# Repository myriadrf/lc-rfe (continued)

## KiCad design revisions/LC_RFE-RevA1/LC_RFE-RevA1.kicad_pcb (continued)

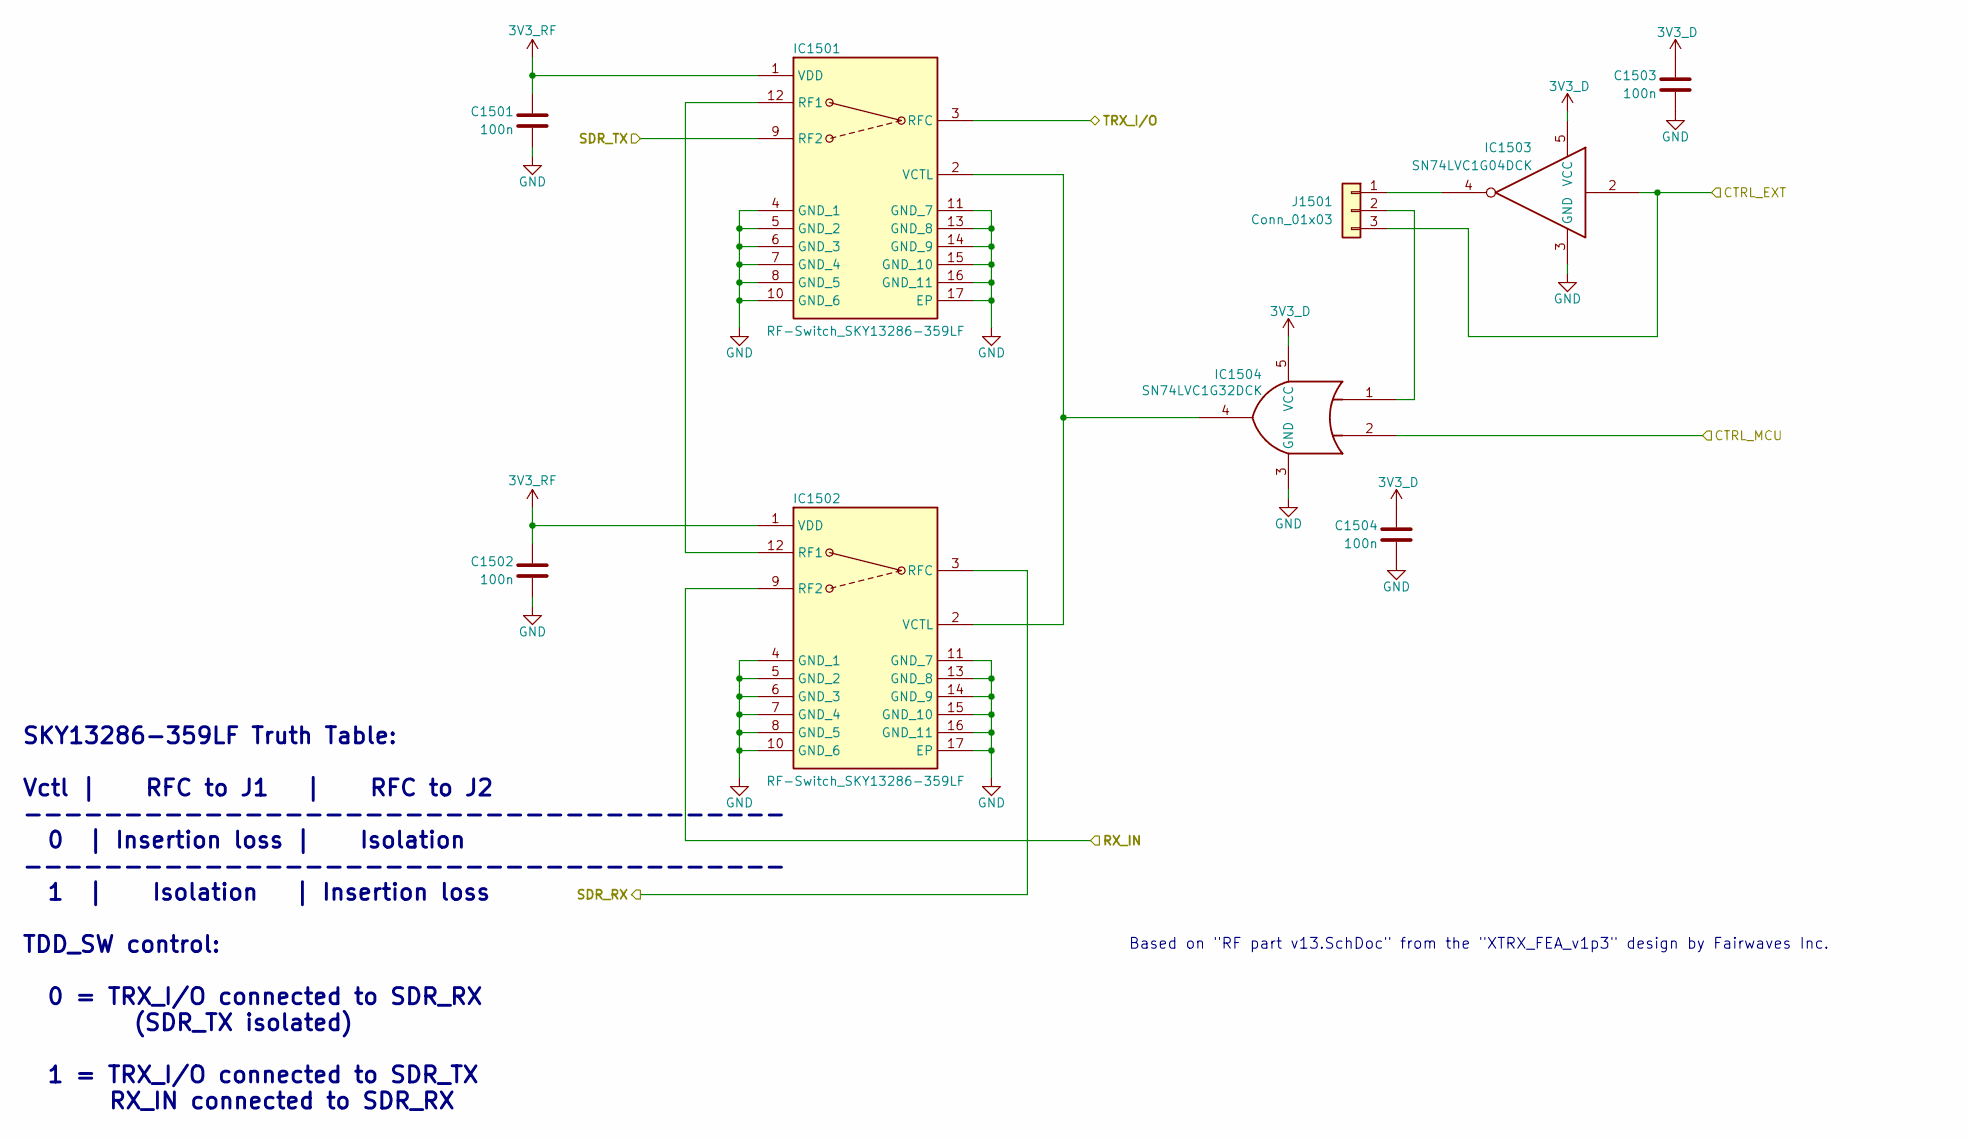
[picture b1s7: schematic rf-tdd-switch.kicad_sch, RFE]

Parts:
C1501, C1502, C1503, C1504: 100n; C_0402_1005Metric; JLCASSY C307331
IC1501, IC1502: RF-Switch_SKY13286-359LF; QFN65P400X400X100-17N-D; Manufacturer_Part_Number SKY13286-359LF; JLCASSY C3304168
IC1503: SN74LVC1G04DCK; SOT-353_SC-70-5; JLCASSY C8207
IC1504: SN74LVC1G32DCK; SOT-353_SC-70-5; JLCASSY C7840
J1501: Conn_01x03; PinHeader_1x03_P2.54mm_Vertical

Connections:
3V3_D: C1503.1, C1504.1, IC1503.5 (VCC), IC1504.5 (VCC); also elsewhere on the board
3V3_RF: C1501.1, C1502.1, IC1501.1 (VDD), IC1502.1 (VDD); also elsewhere on the board
/MCU/STM32_PB6: IC1504.2; also elsewhere on the board
/RF/CH_A_RX: IC1502.9 (RF2); also elsewhere on the board
/RF/CH_A_TRX: IC1501.3 (RFC); also elsewhere on the board
/RF/LNA A/RF_IN: IC1502.3 (RFC); also elsewhere on the board
/RF/PA A/RF_OUT: IC1501.9 (RF2); also elsewhere on the board
GND: C1501.2, C1502.2, C1503.2, C1504.2, IC1501.4 (GND_1), IC1501.5 (GND_2), IC1501.6 (GND_3), IC1501.7 (GND_4), IC1501.8 (GND_5), IC1501.10 (GND_6), IC1501.11 (GND_7), IC1501.13 (GND_8), IC1501.14 (GND_9), IC1501.15 (GND_10), IC1501.16 (GND_11), IC1501.17 (EP), IC1502.4 (GND_1), IC1502.5 (GND_2), IC1502.6 (GND_3), IC1502.7 (GND_4), IC1502.8 (GND_5), IC1502.10 (GND_6), IC1502.11 (GND_7), IC1502.13 (GND_8), IC1502.14 (GND_9), IC1502.15 (GND_10), IC1502.16 (GND_11), IC1502.17 (EP), IC1503.3 (GND), IC1504.3 (GND); also elsewhere on the board
unnamed: IC1501.12 (RF1), IC1502.12 (RF1)
unnamed: IC1501.2 (VCTL), IC1502.2 (VCTL), IC1504.4
unnamed: IC1503.4, J1501.1
unnamed: IC1504.1, J1501.2
TDD_A_CTRL_EXT: IC1503.2, J1501.3; also elsewhere on the board

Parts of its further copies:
C1601, C1602, C1603, C1604: 100n; C_0402_1005Metric; JLCASSY C307331
IC1601, IC1602: RF-Switch_SKY13286-359LF; QFN65P400X400X100-17N-D; Manufacturer_Part_Number SKY13286-359LF; JLCASSY C3304168
IC1603: SN74LVC1G04DCK; SOT-353_SC-70-5; JLCASSY C8207
IC1604: SN74LVC1G32DCK; SOT-353_SC-70-5; JLCASSY C7840
J1601: Conn_01x03; PinHeader_1x03_P2.54mm_Vertical

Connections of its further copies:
3V3_D: C1603.1, C1604.1, IC1603.5 (VCC), IC1604.5 (VCC); also elsewhere on the board
3V3_RF: C1601.1, C1602.1, IC1601.1 (VDD), IC1602.1 (VDD); also elsewhere on the board
/MCU/STM32_PB4: IC1604.2; also elsewhere on the board
/RF/CH_B_RX: IC1602.9 (RF2); also elsewhere on the board
/RF/CH_B_TRX: IC1601.3 (RFC); also elsewhere on the board
/RF/LNA B/RF_IN: IC1602.3 (RFC); also elsewhere on the board
/RF/PA B/RF_OUT: IC1601.9 (RF2); also elsewhere on the board
GND: C1601.2, C1602.2, C1603.2, C1604.2, IC1601.4 (GND_1), IC1601.5 (GND_2), IC1601.6 (GND_3), IC1601.7 (GND_4), IC1601.8 (GND_5), IC1601.10 (GND_6), IC1601.11 (GND_7), IC1601.13 (GND_8), IC1601.14 (GND_9), IC1601.15 (GND_10), IC1601.16 (GND_11), IC1601.17 (EP), IC1602.4 (GND_1), IC1602.5 (GND_2), IC1602.6 (GND_3), IC1602.7 (GND_4), IC1602.8 (GND_5), IC1602.10 (GND_6), IC1602.11 (GND_7), IC1602.13 (GND_8), IC1602.14 (GND_9), IC1602.15 (GND_10), IC1602.16 (GND_11), IC1602.17 (EP), IC1603.3 (GND), IC1604.3 (GND); also elsewhere on the board
unnamed: IC1601.12 (RF1), IC1602.12 (RF1)
unnamed: IC1601.2 (VCTL), IC1602.2 (VCTL), IC1604.4
unnamed: IC1603.4, J1601.1
unnamed: IC1604.1, J1601.2
TDD_B_CTRL_EXT: IC1603.2, J1601.3; also elsewhere on the board

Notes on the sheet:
Based on "RF part v13.SchDoc" from the "XTRX_FEA_v1p3" design by Fairwaves Inc.
SKY13286-359LF Truth Table: Vctl | RFC to J1 | RFC to J2 -------------------------------------- 0 | Insertion loss | Isolation -------------------------------------- 1 | Isolation | Insertion loss TDD_SW control: 0 = TRX_I/O connected to SDR_RX (SDR_TX isolated) 1 = TRX_I/O connected to SDR_TX RX_I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

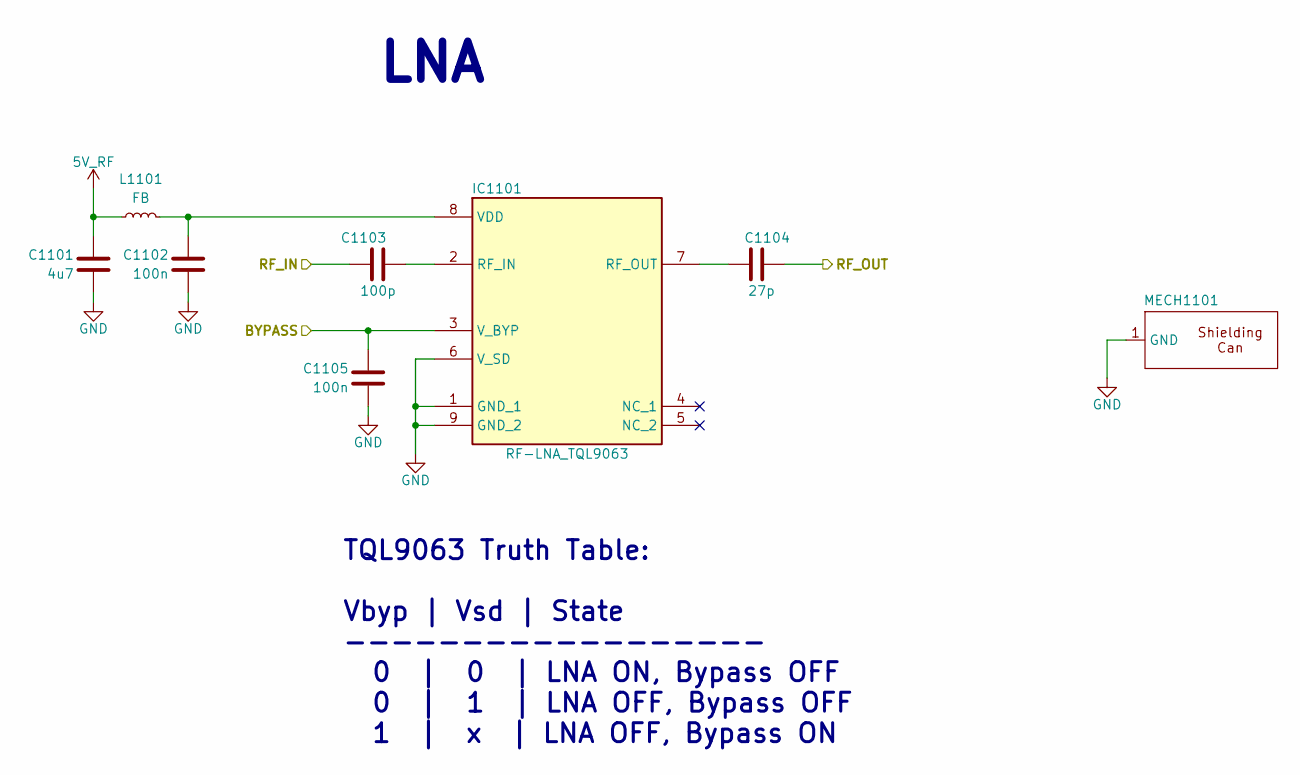
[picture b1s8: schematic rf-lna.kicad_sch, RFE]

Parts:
C1101: 4u7; C_0402_1005Metric; JLCASSY C23733
C1102, C1105: 100n; C_0402_1005Metric; JLCASSY C307331
C1103: 100p; C_0402_1005Metric; JLCASSY C77177
C1104: 27p; C_0402_1005Metric; JLCASSY C1557
IC1101: RF-LNA_TQL9063; SON50P200X200X90-9N; Manufacturer_Part_Number TQL9063; Mouser Part Number 772-TQL9063
L1101: FB; L_0402_1005Metric; JLCASSY C491491
MECH1101: Harwin_S03-15100300R+S0941-46R

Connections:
5V_RF: C1101.1, L1101.1; also elsewhere on the board
/MCU/STM32_PD1: C1105.1, IC1101.3 (V_BYP); also elsewhere on the board
/RF/LNA A/RF_IN: C1103.1; also elsewhere on the board
/RF/LNA A/RF_OUT: C1104.2; also elsewhere on the board
GND: C1101.2, C1102.2, C1105.2, IC1101.1 (GND_1), IC1101.6 (V_SD), IC1101.9 (GND_2), MECH1101.1 (GND); also elsewhere on the board
unnamed: C1103.2, IC1101.2 (RF_IN)
unnamed: C1104.1, IC1101.7 (RF_OUT)
unnamed: C1102.1, IC1101.8 (VDD), L1101.2

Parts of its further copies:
C1201: 4u7; C_0402_1005Metric; JLCASSY C23733
C1202, C1205: 100n; C_0402_1005Metric; JLCASSY C307331
C1203: 100p; C_0402_1005Metric; JLCASSY C77177
C1204: 27p; C_0402_1005Metric; JLCASSY C1557
IC1201: RF-LNA_TQL9063; SON50P200X200X90-9N; Manufacturer_Part_Number TQL9063; Mouser Part Number 772-TQL9063
L1201: FB; L_0402_1005Metric; JLCASSY C491491
MECH1201: Harwin_S03-15100300R+S0941-46R

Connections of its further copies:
5V_RF: C1201.1, L1201.1; also elsewhere on the board
/MCU/STM32_PA15: C1205.1, IC1201.3 (V_BYP); also elsewhere on the board
/RF/LNA B/RF_IN: C1203.1; also elsewhere on the board
/RF/LNA B/RF_OUT: C1204.2; also elsewhere on the board
GND: C1201.2, C1202.2, C1205.2, IC1201.1 (GND_1), IC1201.6 (V_SD), IC1201.9 (GND_2), MECH1201.1 (GND); also elsewhere on the board
unnamed: C1203.2, IC1201.2 (RF_IN)
unnamed: C1204.1, IC1201.7 (RF_OUT)
unnamed: C1202.1, IC1201.8 (VDD), L1201.2

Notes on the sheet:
LNA
TQL9063 Truth Table: Vbyp | Vsd | State ------------------ 0 | 0 | LNA ON, Bypass OFF 0 | 1 | LNA OFF, Bypass OFF 1 | x | LNA OFF, Bypass ON

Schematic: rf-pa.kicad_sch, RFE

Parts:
C1301: 4u7; C_0402_1005Metric; JLCASSY C23733
C1302, C1305: 100n; C_0402_1005Metric; JLCASSY C307331
C1303: 100p; C_0402_1005Metric; JLCASSY C77177
C1304: 27p; C_0402_1005Metric; JLCASSY C1557
IC1301: RF-LNA_TQL9063; SON50P200X200X90-9N; Manufacturer_Part_Number TQL9063; Mouser Part Number 772-TQL9063
L1301: FB; L_0402_1005Metric; JLCASSY C491491
MECH1301: Harwin_S03-15100300R+S0941-46R

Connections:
5V_RF: C1301.1, L1301.1; also elsewhere on the board
/MCU/STM32_PD2: C1305.1, IC1301.3 (V_BYP); also elsewhere on the board
/RF/PA A/RF_IN: C1303.1; also elsewhere on the board
/RF/PA A/RF_OUT: C1304.2; also elsewhere on the board
GND: C1301.2, C1302.2, C1305.2, IC1301.1 (GND_1), IC1301.6 (V_SD), IC1301.9 (GND_2), MECH1301.1 (GND); also elsewhere on the board
unnamed: C1303.2, IC1301.2 (RF_IN)
unnamed: C1304.1, IC1301.7 (RF_OUT)
unnamed: C1302.1, IC1301.8 (VDD), L1301.2

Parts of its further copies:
C1401: 4u7; C_0402_1005Metric; JLCASSY C23733
C1402, C1405: 100n; C_0402_1005Metric; JLCASSY C307331
C1403: 100p; C_0402_1005Metric; JLCASSY C77177
C1404: 27p; C_0402_1005Metric; JLCASSY C1557
IC1401: RF-LNA_TQL9063; SON50P200X200X90-9N; Manufacturer_Part_Number TQL9063; Mouser Part Number 772-TQL9063
L1401: FB; L_0402_1005Metric; JLCASSY C491491
MECH1401: Harwin_S03-15100300R+S0941-46R

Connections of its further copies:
5V_RF: C1401.1, L1401.1; also elsewhere on the board
/MCU/STM32_PD0: C1405.1, IC1401.3 (V_BYP); also elsewhere on the board
/RF/PA B/RF_IN: C1403.1; also elsewhere on the board
/RF/PA B/RF_OUT: C1404.2; also elsewhere on the board
GND: C1401.2, C1402.2, C1405.2, IC1401.1 (GND_1), IC1401.6 (V_SD), IC1401.9 (GND_2), MECH1401.1 (GND); also elsewhere on the board
unnamed: C1403.2, IC1401.2 (RF_IN)
unnamed: C1404.1, IC1401.7 (RF_OUT)
unnamed: C1402.1, IC1401.8 (VDD), L1401.2

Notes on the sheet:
TQL9063 Truth Table: Vbyp | Vsd | State ------------------ 0 | 0 | LNA ON, Bypass OFF 0 | 1 | LNA OFF, Bypass OFF 1 | x | LNA OFF, Bypass ON

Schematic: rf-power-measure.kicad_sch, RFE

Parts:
C902: 4u7; C_0402_1005Metric; JLCASSY C23733
C903, C904, C905, C910, C911, C912: 100n; C_0402_1005Metric; JLCASSY C307331
C906, C907: 1n; C_0402_1005Metric; JLCASSY C126493
C908: 1.8p; C_0402_1005Metric; JLCASSY C85878
C909: 10n; C_0402_1005Metric; not fitted
CON901: uFL; Molex_734120110; MPN HC-RF-IPEX0303-01; JLCASSY C2894919
IC901: RF-PwrDet_LTC5587IDD#TRPBF; SON45P300X300X80-13N-D; Manufacturer_Part_Number LTC5587IDD#TRPBF; Mouser Part Number 584-LTC5587IDD#TRPBF
IC902: Power-VRef_ADR5040BKSZ-REEL7; SOT65P210X110-3N; Manufacturer_Part_Number ADR5040BKSZ-REEL7; Mouser Part Number 584-ADR5040BKSZ-R7
IC903, IC905: RF-Switch-SPDT_SKY13286-359LF; QFN65P400X400X100-17N-D; Manufacturer_Part_Number SKY13286-359LF; JLCASSY C3304168
IC904: RF-Switch-SP3T_SKY13588-460LF; QFN50P200X200X65-13N-D; Manufacturer_Part_Number SKY13588-460LF; Mouser Part Number 873-SKY13588-460LF
L901: FB; L_0402_1005Metric; JLCASSY C491491
L902: 1.5nH; L_0402_1005Metric; JLCASSY C3911113
R901: 390; R_0402_1005Metric; JLCASSY C2906937
R1002: 68 0.1%; R_0402_1005Metric; JLCASSY C317908
TP1001: TestPoint; TestPoint_Pad_D2.0mm

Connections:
3V3_RF: C902.1, C910.1, C911.1, C912.1, IC903.1 (VDD), IC904.6 (VDD), IC905.1 (VDD), L901.1, R901.1; also elsewhere on the board
/MCU/STM32_PA5_SPI1_SCK: IC901.2 (SCK); also elsewhere on the board
/MCU/STM32_PA7_SPI1_MOSI: IC901.1 (SDO); also elsewhere on the board
/MCU/STM32_PA8: IC904.5 (V2); also elsewhere on the board
/MCU/STM32_PB0: IC901.12 (CONV); also elsewhere on the board
/MCU/STM32_PB15: IC904.4 (V1); also elsewhere on the board
/MCU/STM32_PC6: IC905.2 (VCTL); also elsewhere on the board
/MCU/STM32_PC7: IC903.2 (VCTL); also elsewhere on the board
/RF/LNA A/RF_OUT: IC905.9 (RF2); also elsewhere on the board
/RF/PA A/RF_IN: IC904.9 (J2); also elsewhere on the board
/RF/Power Measurement A/SDR_RX: IC905.3 (RFC); also elsewhere on the board
/RF/SDR_CH_A_TX: IC904.11 (RFC); also elsewhere on the board
GND: C902.2, C903.2, C904.2, C905.2, C906.2, C908.2, C909.2, C910.2, C911.2, C912.2, CON901.2 (Ext), IC901.5 (GND_1), IC901.13 (GND_2), IC902.2 (V-), IC903.4 (GND_1), IC903.5 (GND_2), IC903.6 (GND_3), IC903.7 (GND_4), IC903.8 (GND_5), IC903.10 (GND_6), IC903.11 (GND_7), IC903.13 (GND_8), IC903.14 (GND_9), IC903.15 (GND_10), IC903.16 (GND_11), IC903.17 (EP), IC904.2 (GND_1), IC904.7 (GND_2), IC904.8 (GND_3), IC904.10 (GND_4), IC904.12 (GND_5), IC904.13 (EP), IC905.4 (GND_1), IC905.5 (GND_2), IC905.6 (GND_3), IC905.7 (GND_4), IC905.8 (GND_5), IC905.10 (GND_6), IC905.11 (GND_7), IC905.13 (GND_8), IC905.14 (GND_9), IC905.15 (GND_10), IC905.16 (GND_11), IC905.17 (EP), R1002.2; also elsewhere on the board
unnamed: CON901.1 (In), IC903.12 (RF1)
unnamed: C909.1, IC901.6 (CSQ)
unnamed: C903.1, C904.1, C905.1, IC901.3 (OVDD), IC901.8 (VCC), IC901.9 (EN), IC901.11 (VDD), L901.2
unnamed: C907.2, IC901.7 (RF)
unnamed: IC901.10 (VREF), IC902.1 (V+), IC902.3 (T), R901.2
unnamed: IC903.9 (RF2), IC904.3 (J3)
unnamed: C908.1, IC903.3 (RFC), L902.1
unnamed: IC904.1 (J1), IC905.12 (RF1)

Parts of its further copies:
C1002: 4u7; C_0402_1005Metric; JLCASSY C23733
C1003, C1004, C1005, C1010, C1011, C1012: 100n; C_0402_1005Metric; JLCASSY C307331
C1006, C1007: 1n; C_0402_1005Metric; JLCASSY C126493
C1008: 1.8p; C_0402_1005Metric; JLCASSY C85878
C1009: 10n; C_0402_1005Metric; not fitted
CON1001: uFL; Molex_734120110; MPN HC-RF-IPEX0303-01; JLCASSY C2894919
IC1001: RF-PwrDet_LTC5587IDD#TRPBF; SON45P300X300X80-13N-D; Manufacturer_Part_Number LTC5587IDD#TRPBF; Mouser Part Number 584-LTC5587IDD#TRPBF
IC1002: Power-VRef_ADR5040BKSZ-REEL7; SOT65P210X110-3N; Manufacturer_Part_Number ADR5040BKSZ-REEL7; Mouser Part Number 584-ADR5040BKSZ-R7
IC1003, IC1005: RF-Switch-SPDT_SKY13286-359LF; QFN65P400X400X100-17N-D; Manufacturer_Part_Number SKY13286-359LF; JLCASSY C3304168
IC1004: RF-Switch-SP3T_SKY13588-460LF; QFN50P200X200X65-13N-D; Manufacturer_Part_Number SKY13588-460LF; Mouser Part Number 873-SKY13588-460LF
L1001: FB; L_0402_1005Metric; JLCASSY C491491
L1002: 1.5nH; L_0402_1005Metric; JLCASSY C3911113
R902: 68 0.1%; R_0402_1005Metric; JLCASSY C317908
R1001: 390; R_0402_1005Metric; JLCASSY C2906937
TP901: TestPoint; TestPoint_Pad_D2.0mm

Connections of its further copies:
3V3_RF: C1002.1, C1010.1, C1011.1, C1012.1, IC1003.1 (VDD), IC1004.6 (VDD), IC1005.1 (VDD), L1001.1, R1001.1; also elsewhere on the board
/MCU/STM32_PA0_SPI2_SCK: IC1001.2 (SCK); also elsewhere on the board
/MCU/STM32_PA4_SPI2_MOSI: IC1001.1 (SDO); also elsewhere on the board
/MCU/STM32_PA6: IC1001.12 (CONV); also elsewhere on the board
/MCU/STM32_PB11: IC1004.4 (V1); also elsewhere on the board
/MCU/STM32_PB12: IC1004.5 (V2); also elsewhere on the board
/MCU/STM32_PB13: IC1005.2 (VCTL); also elsewhere on the board
/MCU/STM32_PB14: IC1003.2 (VCTL); also elsewhere on the board
/RF/LNA B/RF_OUT: IC1005.9 (RF2); also elsewhere on the board
/RF/PA B/RF_IN: IC1004.9 (J2); also elsewhere on the board
/RF/Power Measurement B/SDR_RX: IC1005.3 (RFC); also elsewhere on the board
/RF/SDR_CH_B_TX: IC1004.11 (RFC); also elsewhere on the board
GND: C1002.2, C1003.2, C1004.2, C1005.2, C1006.2, C1008.2, C1009.2, C1010.2, C1011.2, C1012.2, CON1001.2 (Ext), IC1001.5 (GND_1), IC1001.13 (GND_2), IC1002.2 (V-), IC1003.4 (GND_1), IC1003.5 (GND_2), IC1003.6 (GND_3), IC1003.7 (GND_4), IC1003.8 (GND_5), IC1003.10 (GND_6), IC1003.11 (GND_7), IC1003.13 (GND_8), IC1003.14 (GND_9), IC1003.15 (GND_10), IC1003.16 (GND_11), IC1003.17 (EP), IC1004.2 (GND_1), IC1004.7 (GND_2), IC1004.8 (GND_3), IC1004.10 (GND_4), IC1004.12 (GND_5), IC1004.13 (EP), IC1005.4 (GND_1), IC1005.5 (GND_2), IC1005.6 (GND_3), IC1005.7 (GND_4), IC1005.8 (GND_5), IC1005.10 (GND_6), IC1005.11 (GND_7), IC1005.13 (GND_8), IC1005.14 (GND_9), IC1005.15 (GND_10), IC1005.16 (GND_11), IC1005.17 (EP), R902.2; also elsewhere on the board
unnamed: CON1001.1 (In), IC1003.12 (RF1)
unnamed: C1009.1, IC1001.6 (CSQ)
unnamed: C1003.1, C1004.1, C1005.1, IC1001.3 (OVDD), IC1001.8 (VCC), IC1001.9 (EN), IC1001.11 (VDD), L1001.2
unnamed: C1007.2, IC1001.7 (RF)
unnamed: IC1001.10 (VREF), IC1002.1 (V+), IC1002.3 (T), R1001.2
unnamed: IC1003.9 (RF2), IC1004.3 (J3)
unnamed: C1008.1, IC1003.3 (RFC), L1002.1
unnamed: IC1004.1 (J1), IC1005.12 (RF1)

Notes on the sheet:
RFin match for freq. range: 1.75 to 2.2GHz See pg.12 in datasheet for details
2.048V ±0.1 Voltage Reference
- OVdd: ADC Output Driver Supply - Vcc: Detector Power Supply - Vref: ADC Reference Input Voltage - Vdd: ADC Power Supply

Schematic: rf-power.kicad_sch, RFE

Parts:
C601: 22u; C_1206_3216Metric; JLCASSY C478862
C602, C604: 100n; C_0402_1005Metric; JLCASSY C307331
C603: 4u7; C_0402_1005Metric; JLCASSY C23733
IC601: Power-LDO_NCP59800BMNADJTBG; DFN-8(3x3); Manufacturer_Part_Number NCP59800BMNADJTBG; Mouser Part Number 863-NCP59800BMNADJTB
L601: FB; L_0402_1005Metric; JLCASSY C491491
R601: 30K9; R_0402_1005Metric; JLCASSY C852715
R602: 10K; R_0402_1005Metric; JLCASSY C2902636

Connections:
3V3_RF: C603.1, IC601.1 (OUT_1), IC601.2 (OUT_2), R601.1; also elsewhere on the board
5V_RF: C602.1, IC601.5 (EN), IC601.7 (IN_1), IC601.8 (IN_2), L601.2; also elsewhere on the board
GND: C601.2, C602.2, C603.2, C604.2, IC601.4 (GND), IC601.EP, R602.2; also elsewhere on the board
unnamed: IC601.3 (FB/SNS), R601.2, R602.1
unnamed: C604.1, IC601.6 (NR)
VUSB: C601.1, L601.1; also elsewhere on the board

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
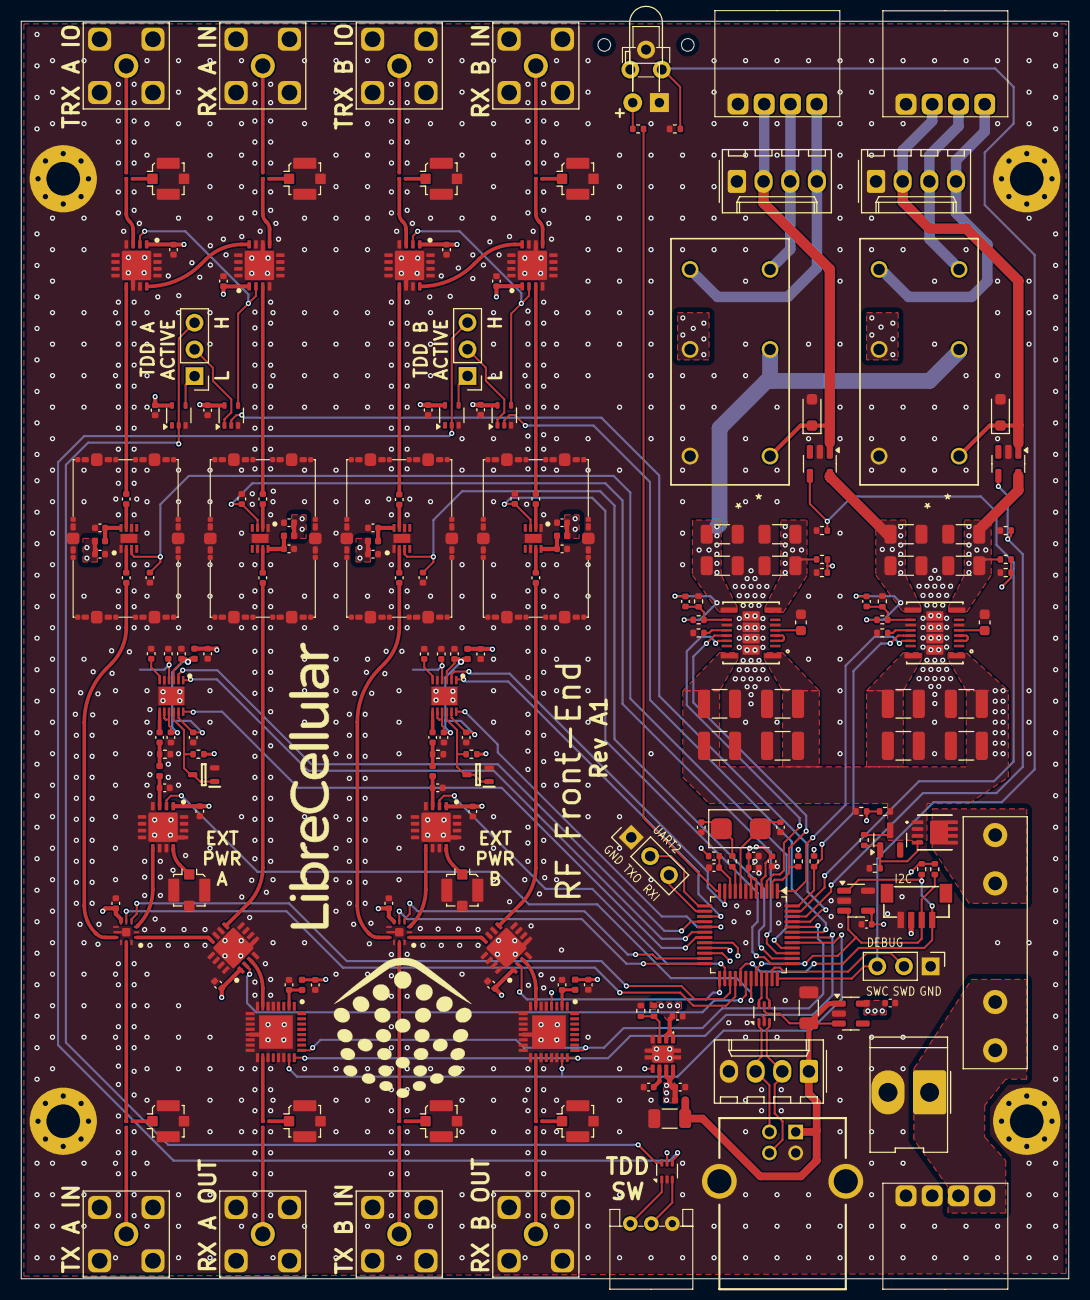
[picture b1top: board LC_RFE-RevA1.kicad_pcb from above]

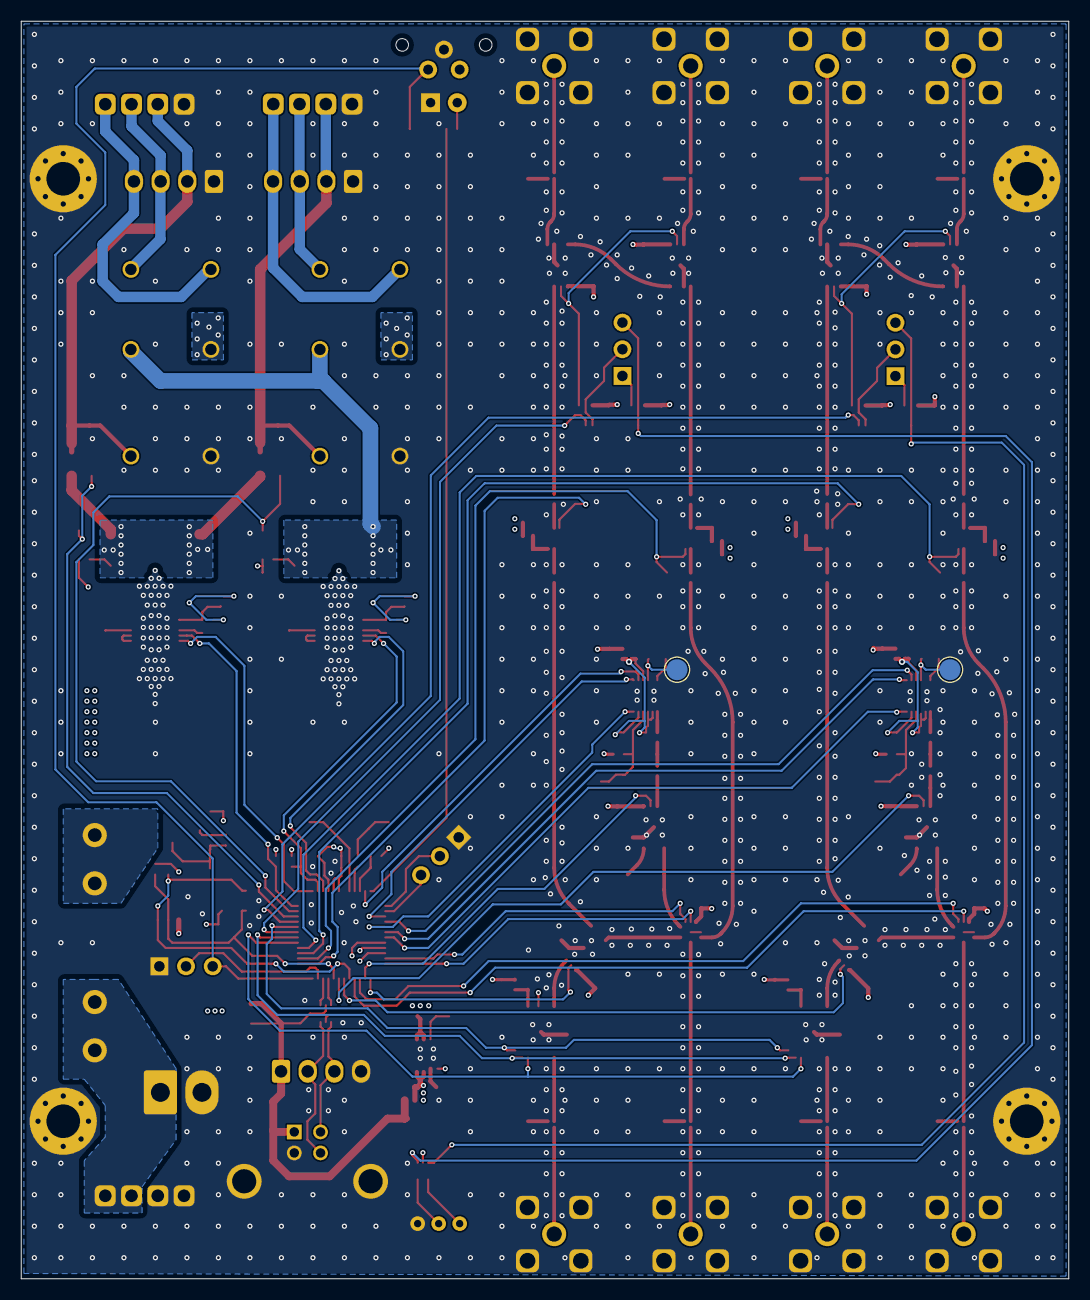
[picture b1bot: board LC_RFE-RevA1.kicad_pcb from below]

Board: 4 copper layers, 99.7 x 119.7 mm, 231 parts (2 on the bottom side), 155 nets.

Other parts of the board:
Ref**: Val**; LibreCellular_Logo

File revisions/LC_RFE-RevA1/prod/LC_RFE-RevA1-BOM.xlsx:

Value | Designator | JLCASSY | Footprint
8MHz | Y301 | C3035202 | LC_RFE:Crystal_SMD_5032-2Pin_5.0x3.2mm
TestPoint | TP901,TP1001 |  | TestPoint:TestPoint_Pad_D2.0mm
TCB73B-H048-L1 | SW301 | C2890354 | LC_RFE:PushButton-TCB73B-H048-L1
68 0.1% | R902,R1002 | C317908 | Resistor_SMD:R_0402_1005Metric
30K9 | R601 | C852715 | Resistor_SMD:R_0402_1005Metric
0 | R501,R503,R505,R507,R509,R511,R513,R515 | C106227 | LC_RFE:0201-SQUARE
3.3K | R304,R305 | C25890 | Resistor_SMD:R_0402_1005Metric
2.2K | R303 | C25879 | Resistor_SMD:R_0402_1005Metric
390 | R302,R901,R1001 | C2906937 | Resistor_SMD:R_0402_1005Metric
12.1K | R208 | C281773 | Resistor_SMD:R_0402_1005Metric
40.2K 0.1% | R205 | C852775 | Resistor_SMD:R_0402_1005Metric
6.98K 1% | R204 | C47500 | Resistor_SMD:R_0402_1005Metric
110K 0.1% | R201 | C517659 | Resistor_SMD:R_0402_1005Metric
75K 0.1% | R105 | C319479 | Resistor_SMD:R_0402_1005Metric
26.1K 0.1% | R104,R106,R107,R108 | C728557 | Resistor_SMD:R_0402_1005Metric
191K 0.1% | R103 | C2441163 | Resistor_SMD:R_0402_1005Metric
10K | R102,R202,R203,R206,R207,R301,R306,R401,R402,R602 | C2902636 | Resistor_SMD:R_0402_1005Metric
BSZ086P03NS3G | Q101 | C459171 | LC_RFE:TSDSON-8(3.3x3.3)
1.5nH | L902,L1002 | C3911113 | Inductor_SMD:L_0402_1005Metric
FB | L601,L701,L801,L901,L1001,L1101,L1201,L1301,L1401 | C491491 | Inductor_SMD:L_0402_1005Metric
SN74LVC1G32DCK | IC1504,IC1604 | C7840 | Package_TO_SOT_SMD:SOT-353_SC-70-5
SN74LVC1G04DCK | IC1503,IC1603 | C8207 | Package_TO_SOT_SMD:SOT-353_SC-70-5
RF-Switch_SKY13286-359LF | IC1501,IC1502,IC1601,IC1602 | C3304168 | LC_RFE:QFN65P400X400X100-17N-D
RF-LNA_TQL9063 | IC1101,IC1201,IC1301,IC1401 | C5346221 | LC_RFE:SON50P200X200X90-9N
RF-Switch-SP3T_SKY13588-460LF | IC904,IC1004 | C2151906 | LC_RFE:QFN50P200X200X65-13N-D
RF-Switch-SPDT_SKY13286-359LF | IC903,IC905,IC1003,IC1005 | C3304168 | LC_RFE:QFN65P400X400X100-17N-D
Power-VRef_ADR5040BKSZ-REEL7 | IC902,IC1002 | C659592 | SOT65P210X110-3N
RF-PwrDet_LTC5587IDD#TRPBF | IC901,IC1001 | C688698 | LC_RFE:SON45P300X300X80-13N-D
RF-Attenuator_F1956NBGI8 | IC701,IC801 | C1511898 | LC_RFE:QFN50P500X500X80-33N-D
Power-LDO_NCP59800BMNADJTBG | IC601 | C464053 | LC_RFE:DFN-8(3x3)
RT9742CGJ5 | IC401,IC402 | C250546 | Package_TO_SOT_SMD:TSOT-23-5
FT24C32A-ELR-T | IC303 | C5263776 | Package_TO_SOT_SMD:SOT-23-5
TPS7A0533PDBV | IC302 | C493453 | Package_TO_SOT_SMD:SOT-23-5
STM32G0B1CBTx | IC301 | C2847904 | Package_QFP:LQFP-48_7x7mm_P0.5mm
Power-Buck_TPSM63604RDLR | IC201,IC202 | C5219289 | LC_RFE:B3QFN-20(5.0x5.5)-RDL0020A
01000020Z | F101 | C142797 | LC_RFE:Fuseholder_2x_Littelfuse_100_series_5x20mm
D_Schottky | D401,D402 | C191023 | Diode_SMD:D_SOD-323_HandSoldering
USBLC6-2P6 | D102,D501 | C15999 | LC_RFE:SOT-666
BZX84C12LT1G | D101 | C82475 | Package_TO_SOT_SMD:SOT-23
uFL | CON509,CON510,CON511,CON512,CON513,CON514,CON515,CON516,CON901,CON1001 | C2894919 | LC_RFE:Molex_734120110
27p | C1104,C1204,C1304,C1404 | C1557 | Capacitor_SMD:C_0402_1005Metric
100p | C1103,C1203,C1303,C1403 | C77177 | Capacitor_SMD:C_0402_1005Metric
1.8p | C908,C1008 | C85878 | Capacitor_SMD:C_0402_1005Metric
1n | C906,C907,C1006,C1007 | C126493 | Capacitor_SMD:C_0402_1005Metric
18p | C305,C306 | C1549 | Capacitor_SMD:C_0402_1005Metric
100n | C302,C303,C304,C309,C602,C604,C702,C802,C903,C904,C905,C910,C911,C912,C1003,C10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 | C307331 | Capacitor_SMD:C_0402_1005Metric
4u7 | C301,C308,C603,C701,C801,C902,C1002,C1101,C1201,C1301,C1401 | C23733 | Capacitor_SMD:C_0402_1005Metric
8.2p | C216 | C1579 | Capacitor_SMD:C_0402_1005Metric
22u | C207,C208,C209,C210,C217,C218,C219,C220,C307,C601 | C478862 | Capacitor_SMD:C_1206_3216Metric
1u | C205,C215 | C519560 | Capacitor_SMD:C_0603_1608Metric
10u | C201,C202,C203,C204,C211,C212,C213,C214 | C597578 | Capacitor_SMD:C_1210_3225Metric

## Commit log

2024-07-11 init
2024-07-11 initial release for libs, panels and RevA1
2024-07-12 Add licence and update README.
2025-05-10 lib updates
2025-05-10 RevA1 schematic cleanup
2025-05-10 RevA2 initial commit
2025-06-03 Update image
2025-06-03 Add new image.
